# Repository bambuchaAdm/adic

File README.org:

* ADIC Tape library

English version below →

** Wersja polska

Zewstaw dokumentacji płytek oraz schematów użytych 
do uruchomienia oraz postawienia wstan gotowośći
biblioteki taśmowej Hackerspace Kraków.

---

** English version

A set of documentation, circuits and schematics used to
make  hackerspaces tape library running.

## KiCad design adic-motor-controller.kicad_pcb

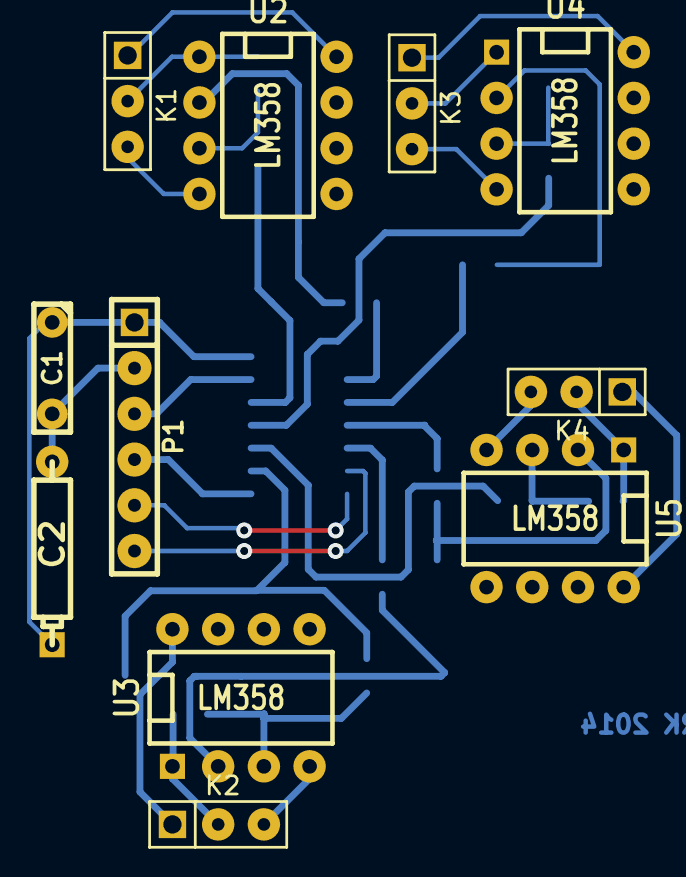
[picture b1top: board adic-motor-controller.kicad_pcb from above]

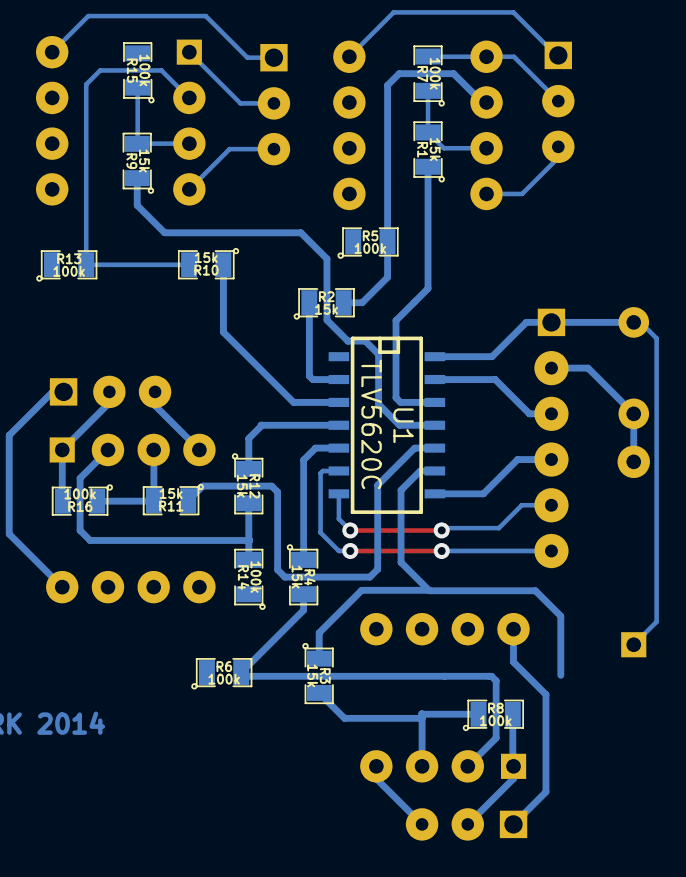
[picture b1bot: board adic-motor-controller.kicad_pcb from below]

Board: 2 copper layers, 28 parts (17 on the bottom side), 34 nets.

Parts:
C1: 10n; C2
C2: 4u7; CP4
K1, K2, K3, K4: CONN_3; PIN_ARRAY_3X1
P1: CONN_6; PIN_ARRAY-6X1
R1, R2, R3, R4, R9, R10, R11, R12: 15k; SM0805
R5, R6, R7, R8, R13, R14, R15, R16: 100k; SM0805
U1: TLV5620C; SO14E
U2, U3, U4, U5: LM358; DIP-8__300

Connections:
GND: C1.2, C2.2, P1.2, R5.1, R6.1, R13.1, R14.1, U1.1, U2.5, U2.6, U3.5, U3.6, U4.5, U4.6, U5.5, U5.6
unnamed: P1.6, U1.6
unnamed: P1.5, U1.7
unnamed: P1.4, U1.8
unnamed: R10.1, U1.3
unnamed: K1.3, U2.4
unnamed: K1.1, U2.8
unnamed: P1.3, U1.13
unnamed: R9.1, U1.11
unnamed: C1.1, C2.1, P1.1, U1.14
unnamed: R1.1, U1.12
unnamed: K3.2, R15.2, U4.1
unnamed: R9.2, R15.1, U4.3
unnamed: R10.2, R13.2, U4.2
unnamed: K4.2, R16.2, U5.1
unnamed: R2.1, U1.2
unnamed: R11.1, U1.10
unnamed: R12.1, U1.4
unnamed: R3.1, U1.9
unnamed: R4.1, U1.5
unnamed: K3.1, U4.8
unnamed: K3.3, U4.4
unnamed: K2.3, U3.4
unnamed: K2.1, U3.8
unnamed: K4.1, U5.8
unnamed: K4.3, U5.4
unnamed: K1.2, R7.2, U2.1
unnamed: R11.2, R16.1, U5.3
unnamed: K2.2, R8.2, U3.1
unnamed: R4.2, R6.2, U3.2
unnamed: R3.2, R8.1, U3.3
unnamed: R12.2, R14.2, U5.2
unnamed: R1.2, R7.1, U2.3
unnamed: R2.2, R5.2, U2.2

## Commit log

2013-11-20 Init import Dodanie złączy wyjściowych na każdy kanał.
2013-11-20 Change output type.
2013-11-20 Rename after first test name.
2013-11-20 Add README.
2013-11-22 Create board from schema.
2014-02-11 Add GND net connection to op-ams
2014-02-11 Add result SVG.
2015-02-14 Zwarcie nieużywanych wejść do masy.
    Zmiana planowania. Rozszenie możliwośći.
